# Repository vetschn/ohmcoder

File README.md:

# 

The `OHMCODER` is a 16 channel fully analog vocoder, housed in a 3U 19"
enclosure with a full patch bay and feed-through functionality.

This project is inspired by [this](https://www.instructables.com/Build-an-analog-vocoder/) instructables project by user [planetone](https://www.instructables.com/member/planetone/).

## Overview

In vocoders, a program and carrier signal are filtered into a number of
frequency bands. The envelope of the program signal bands then modulates
the carrier signal bands. Finally, the per-band contributions are summed
back together to get the vocoded output.

The core of the design thus made up of

- [Bandpass Filters](#multiple-feedback-infinite-gain-bandpass-filters)
- [Envelope Followers](#envelope-followers)
- [Voltage Controlled Amplifiers](#ota-voltage-controlled-amplifiers)

## Features

<!-- TODO -->

- Jack and XLR Input
- Patch Bay
- Per-Band Gain Control with LED Indicators
- Program or Carrier Band Feed-Through and/or Mixing
- Stereo and Mono Jack Output

## Circuits

### Multiple-Feedback Infinite Gain Bandpass Filters

We used the same second order multiple-feedback infinite-gain active
bandpass filters as in the instructibles project. TL074 quad opamps are
used.

Notice, that the nice thing about these filters is, that we only need to
change the capacitor values to get different center frequencies, as seen
in the SPICE simulation below.

#### Capacitor Values

| Band | f_low [Hz] | f_high [Hz] | C [nF] |
| ---- | ---------- | ----------- | ------ |
| 01   | 65         | 105         | 0.91   |
| 02   | 90         | 150         | 1.3    |
| 03   | 125        | 200         | 1.8    |
| 04   | 175        | 285         | 2.4    |
| 05   | 255        | 400         | 3.3    |
| 06   | 345        | 555         | 4.7    |
| 07   | 465        | 755         | 6.8    |
| 08   | 635        | 1050        | 9.1    |
| 09   | 920        | 1455        | 13     |
| 10   | 1220       | 1960        | 18     |
| 11   | 1765       | 2880        | 24     |
| 12   | 2500       | 4075        | 33     |
| 13   | 3515       | 5605        | 47     |
| 14   | 4640       | 7550        | 68     |
| 15   | 6375       | 10375       | 91     |
| 16   | 9200       | 15000       | 130    |

### Envelope Followers

This is where we depart from planetone's design. We use a low-pass
filtered precision rectifier signal to follow the program envelope.

The majority of the spectral energy of speech amplitude modulation lies
below about 15Hz, i. e. the mean time between syllables is about
1/15Hz (see [speech_modulation.ipynb](./auxiliary/notebooks/speech_modulation.ipynb) for an example). The filter is chosen such that we follow this
amplitude modulation.

### OTA Voltage Controlled Amplifiers

We use VCAs based on the LM13700 quad operational transconductance
amplifier, making use of its linearizing diodes and the integrated
buffer circuits.

The program envelope controls the amplifier gain via a voltage to
current converter circuit.

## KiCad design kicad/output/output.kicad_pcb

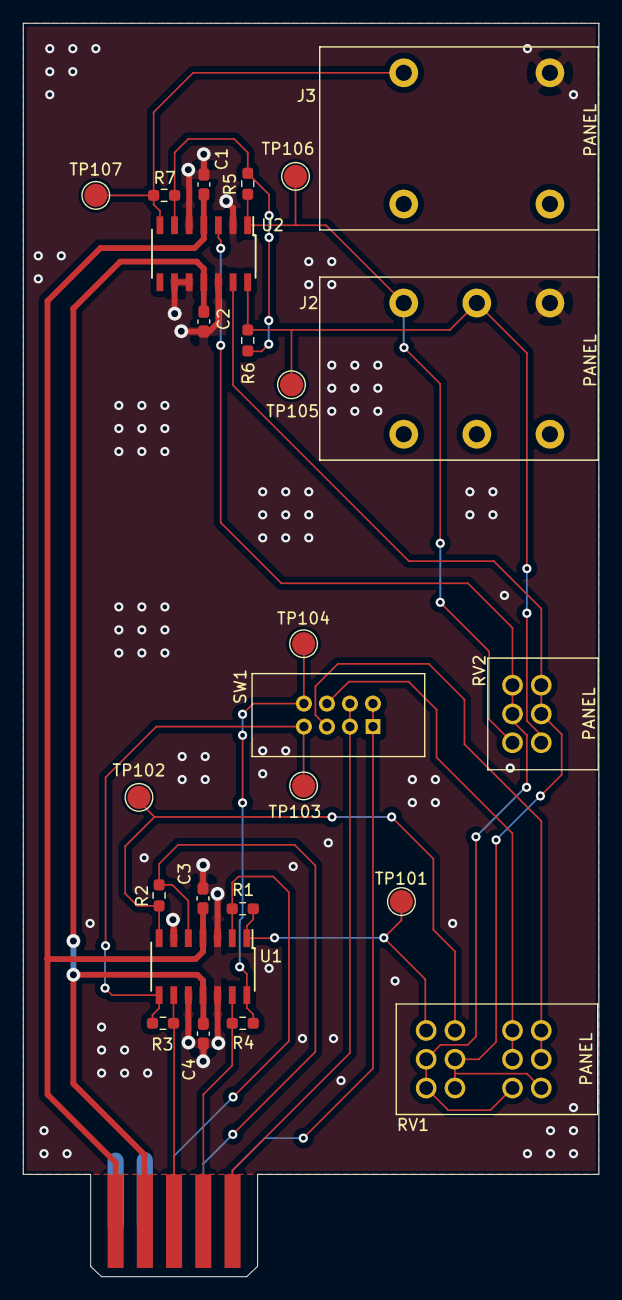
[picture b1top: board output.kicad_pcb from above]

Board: 2 copper layers, 50.0 x 108.9 mm, 26 parts (0 on the bottom side), 21 nets.

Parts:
C1, C2, C3, C4: 100n; C_0603_1608Metric_Pad1.08x0.95mm_HandSolder
J1: Conn_02x05_Odd_Even; 345-010-521-201_Male
J2: AudioJack3_Switch; Amphenol_ACJS-MHDRM
J3: AudioJack2_Switch; Amphenol_ACJM-MHDRM
R1, R2, R3, R4, R5, R6, R7: 10k; R_0603_1608Metric_Pad0.98x0.95mm_HandSolder
RV1: 10k; Bourns_PTD904-2020K-B103
RV2: 20k; Bourns_PTD902-2020K-A203
SW1: SW_DP3T; Hirose-DF51A-8DP-2DSA
TP101, TP102, TP103, TP104, TP105, TP106, TP107: TestPoint; TestPoint_Pad_D2.0mm
U1, U2: TL074; TL074-SOIC-14

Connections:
+12V: C1.1, C3.1, J1.1, U1.4, U2.4
-12V: C2.2, C4.2, J1.3, U1.11, U2.11
/CARRIER: J1.10, SW1.1, SW1.5
/FEEDTHROUGH_LEFT: RV1.R22, RV1.R23, SW1.7
/FEEDTHROUGH_RIGHT: RV1.R12, RV1.R13, SW1.3
/MOD_CARRIER_BANDS_LEFT: J1.6, R1.2, U1.2
/MOD_CARRIER_BANDS_LEFT_BUFFERED: R1.1, RV1.R43, TP101.1, U1.1
/MOD_CARRIER_BANDS_RIGHT: J1.8, R2.2, U1.5
/MOD_CARRIER_BANDS_RIGHT_BUFFERED: R2.1, RV1.R33, TP102.1, U1.7
/PROGRAM: J1.9, SW1.2, SW1.6
/PROGRAM_BANDS_LEFT: J1.5, R3.2, U1.9
/PROGRAM_BANDS_LEFT_BUFFERED: R3.1, SW1.4, TP103.1, U1.8
/PROGRAM_BANDS_RIGHT: J1.7, R4.2, U1.13
/PROGRAM_BANDS_RIGHT_BUFFERED: R4.1, SW1.8, TP104.1, U1.14
GND: C1.2, C2.1, C3.2, C4.1, J1.2, J1.4, J2.S, J3.S, U1.3, U1.6, U1.10, U1.12, U2.2, U2.5, U2.9, U2.10, U2.12
unnamed: J2.R, R6.2, RV2.4, TP105.1, U2.14
unnamed: J2.T, R5.1, RV2.1, TP106.1, U2.1
unnamed: J3.T, R7.2, TP107.1, U2.7
unnamed: R5.2, R6.1, R7.1, U2.6
unnamed: RV1.R11, RV1.R31, RV1.R32, RV2.5, RV2.6, U2.13
unnamed: RV1.R21, RV1.R41, RV1.R42, RV2.2, RV2.3, U2.3

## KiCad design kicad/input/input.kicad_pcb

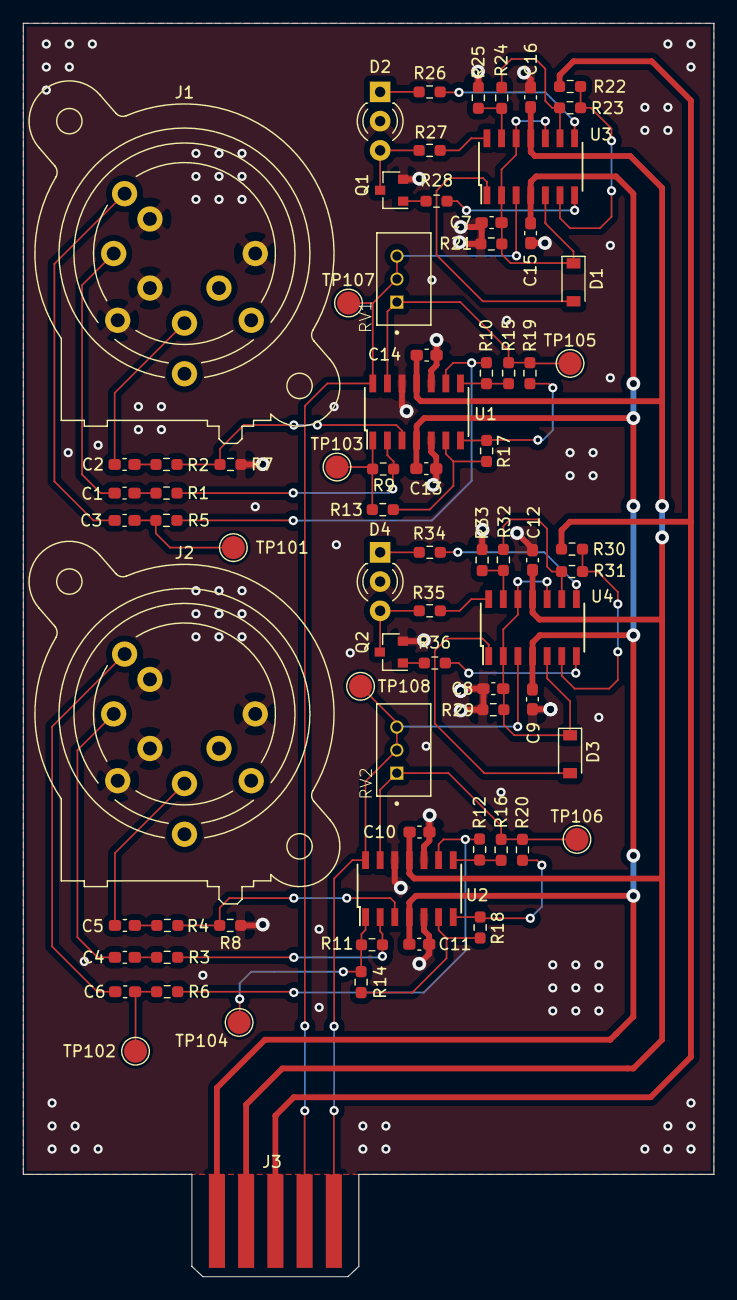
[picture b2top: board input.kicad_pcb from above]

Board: 2 copper layers, 60.0 x 108.9 mm, 75 parts (0 on the bottom side), 56 nets.

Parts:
C1, C2, C4, C5: 4.7u; C_0603_1608Metric_Pad1.08x0.95mm_HandSolder
C3, C6, C7, C8: 10u; C_0603_1608Metric_Pad1.08x0.95mm_HandSolder
C9, C10, C11, C12, C13, C14, C15, C16: 100n; C_0603_1608Metric_Pad1.08x0.95mm_HandSolder
D1, D3: 1N4148; D_SOD-123
D2, D4: LED_Dual_ACA; LED_D3.0mm-3
J1, J2: XLR3_AudioJack3_Combo_Switch; Jack_XLR-6.35mm_Neutrik_NCJ9FI-V_Vertical
J3: Conn_02x05_Odd_Even; 345-010-521-201_Male
Q1, Q2: MMBTA42; SOT-23
R1, R2, R3, R4, R13, R14, R28, R36: 1k; R_0603_1608Metric_Pad0.98x0.95mm_HandSolder
R5, R6, R7, R8, R9, R10, R11, R12, R15, R16, R17, R18, R19, R20: 10k; R_0603_1608Metric_Pad0.98x0.95mm_HandSolder
R21, R29: 4.7k; R_0603_1608Metric_Pad0.98x0.95mm_HandSolder
R22, R30: 27k; R_0603_1608Metric_Pad0.98x0.95mm_HandSolder
R23, R31: 18k; R_0603_1608Metric_Pad0.98x0.95mm_HandSolder
R24, R32: 33k; R_0603_1608Metric_Pad0.98x0.95mm_HandSolder
R25, R33: 22k; R_0603_1608Metric_Pad0.98x0.95mm_HandSolder
R26, R27, R34, R35: 470; R_0603_1608Metric_Pad0.98x0.95mm_HandSolder
RV1, RV2: 50k; TE-6-440054-3
TP101, TP102, TP103, TP104, TP105, TP106, TP107, TP108: TestPoint; TestPoint_Pad_D2.0mm
U1, U2, U3, U4: TL074; TL074-SOIC-14

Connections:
+2V: J3.5, R22.1, R30.1
+12V: C9.1, C11.1, C13.1, C15.1, J3.1, U1.4, U2.4, U3.4, U4.4
-12V: C10.2, C12.2, C14.2, C16.2, J3.3, U1.11, U2.11, U3.11, U4.11
/CARRIER: J3.9, RV2.2, RV2.3, TP108.1, U2.14, U4.3
/PROGRAM: J3.7, RV1.2, RV1.3, TP107.1, U1.14, U3.3
GND: C7.2, C8.2, C9.2, C10.1, C11.2, C12.1, C13.2, C14.1, C15.2, C16.1, D2.2, D4.2, J1.1, J1.S, J1.SN, J1.TN, J2.1, J2.S, J2.SN, J2.TN, J3.2, J3.4, J3.6, J3.8, J3.10, Q1.2, Q2.2, R7.2, R8.2, R21.2, R25.2, R29.2, R33.2, U1.5, U1.10, U1.12, U2.5, U2.10, U2.12
unnamed: C1.1, R1.2
unnamed: C1.2, J1.2
unnamed: C2.1, R2.2
unnamed: C2.2, J1.3
unnamed: C3.1, R5.2, TP101.1
unnamed: C3.2, J1.T
unnamed: C4.1, R3.2
unnamed: C4.2, J2.2
unnamed: C5.1, R4.2
unnamed: C5.2, J2.3
unnamed: C6.1, R6.2, TP102.1
unnamed: C6.2, J2.T
unnamed: C7.1, D1.1, R21.1, U3.2, U3.5, U3.10, U3.12
unnamed: C8.1, D3.1, R29.1, U4.2, U4.5, U4.10, U4.12
unnamed: D1.2, U3.1
unnamed: D2.1, R26.1
unnamed: D2.3, Q1.3, R27.1
unnamed: D3.2, U4.1
unnamed: D4.1, R34.1
unnamed: D4.3, Q2.3, R35.1
unnamed: Q1.1, R28.2
unnamed: Q2.1, R36.2
unnamed: R1.1, R9.2, U1.2
unnamed: R2.1, R7.1, U1.3
unnamed: R4.1, R8.1, U2.3
unnamed: R10.1, R15.1, U1.8
unnamed: R5.1, R10.2, U1.9
unnamed: R11.1, R14.2, TP104.1, U2.1
unnamed: R3.1, R11.2, U2.2
unnamed: R12.1, R16.1, U2.8
unnamed: R6.1, R12.2, U2.9
unnamed: R13.1, R17.2, U1.6
unnamed: R9.1, R13.2, TP103.1, U1.1
unnamed: R14.1, R18.2, U2.6
unnamed: R15.2, R19.1, RV1.1, TP105.1, U1.13
unnamed: R16.2, R20.1, RV2.1, TP106.1, U2.13
unnamed: R17.1, R19.2, U1.7
unnamed: R18.1, R20.2, U2.7
unnamed: R22.2, R23.1, U3.6
unnamed: R23.2, R24.1, U3.9
unnamed: R24.2, R25.1, U3.13
unnamed: R26.2, U3.8
unnamed: R27.2, U3.14
unnamed: R28.1, U3.7
unnamed: R30.2, R31.1, U4.6
unnamed: R31.2, R32.1, U4.9
unnamed: R32.2, R33.1, U4.13
unnamed: R34.2, U4.8
unnamed: R35.2, U4.14
unnamed: R36.1, U4.7

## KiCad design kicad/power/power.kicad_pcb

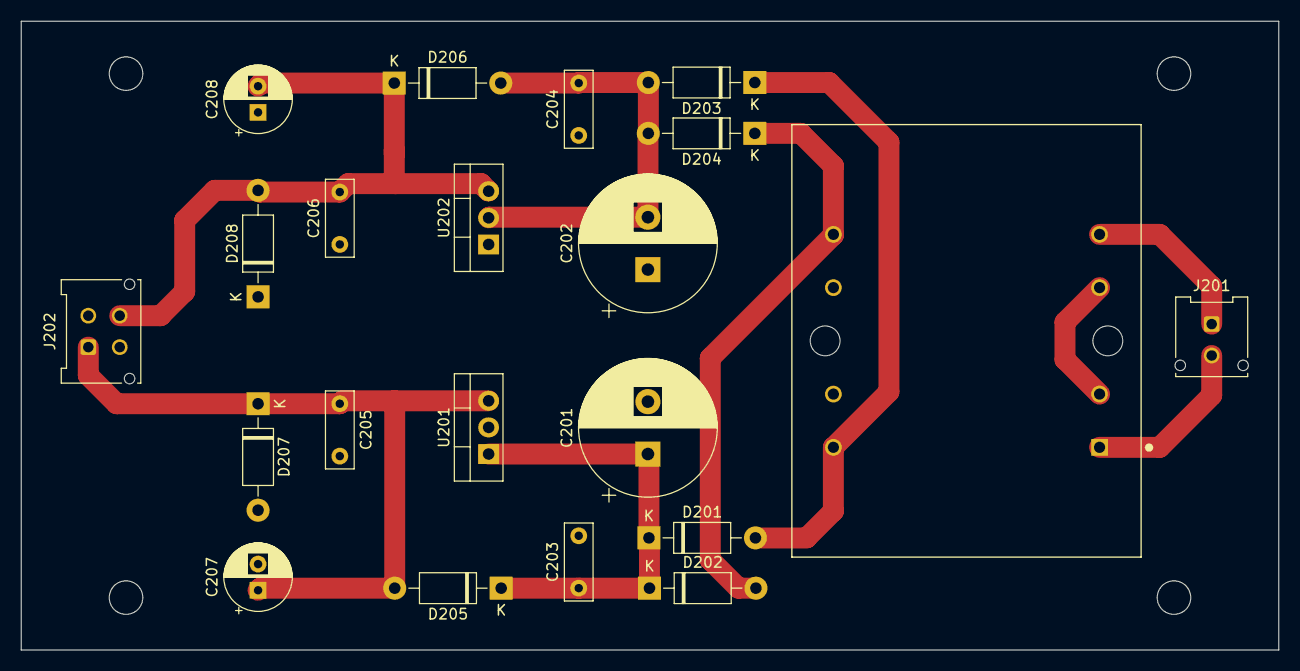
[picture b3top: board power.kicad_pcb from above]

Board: 2 copper layers, 120.0 x 60.0 mm, 21 parts (0 on the bottom side), 10 nets.

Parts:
C201, C202: 2200u; CP_Radial_D13.0mm_P5.00mm
C203, C204, C205, C206: 100n; C_Rect_L7.2mm_W2.5mm_P5.00mm_FKS2_FKP2_MKS2_MKP2
C207, C208: 100u; CP_Radial_D6.3mm_P2.50mm
D201, D202, D203, D204, D205, D206, D207, D208: 1N4002; D_DO-41_SOD81_P10.16mm_Horizontal
J201: Conn_01x02_Female; Molex_Micro-Fit_3.0_43045-0212_2x01_P3.00mm_Vertical
J202: Conn_02x02_Odd_Even; Molex_Micro-Fit_3.0_43045-0412_2x02_P3.00mm_Vertical
T201: VPP36-140; XFMR_VPP36-140
U201: uA7812; TO-220-3_Vertical
U202: uA7912; TO-220-3_Vertical

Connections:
+12V: C205.1, C207.1, D205.2, D207.1, J202.1, U201.3
-12V: C206.2, C208.2, D206.1, D208.2, J202.4, U202.3
GND: C201.2, C202.1, C203.2, C204.1, C205.2, C206.1, C207.2, C208.1, D207.2, D208.1, J202.2, J202.3, T201.9, T201.10, U201.2, U202.1
unnamed: C201.1, C203.1, D201.1, D202.1, D205.1, U201.1
unnamed: C202.2, C204.2, D203.2, D204.2, D206.2, U202.2
unnamed: D201.2, D203.1, T201.7
unnamed: D202.2, D204.1, T201.12
unnamed: J201.1, T201.6
unnamed: J201.2, T201.1
unnamed: T201.3, T201.4

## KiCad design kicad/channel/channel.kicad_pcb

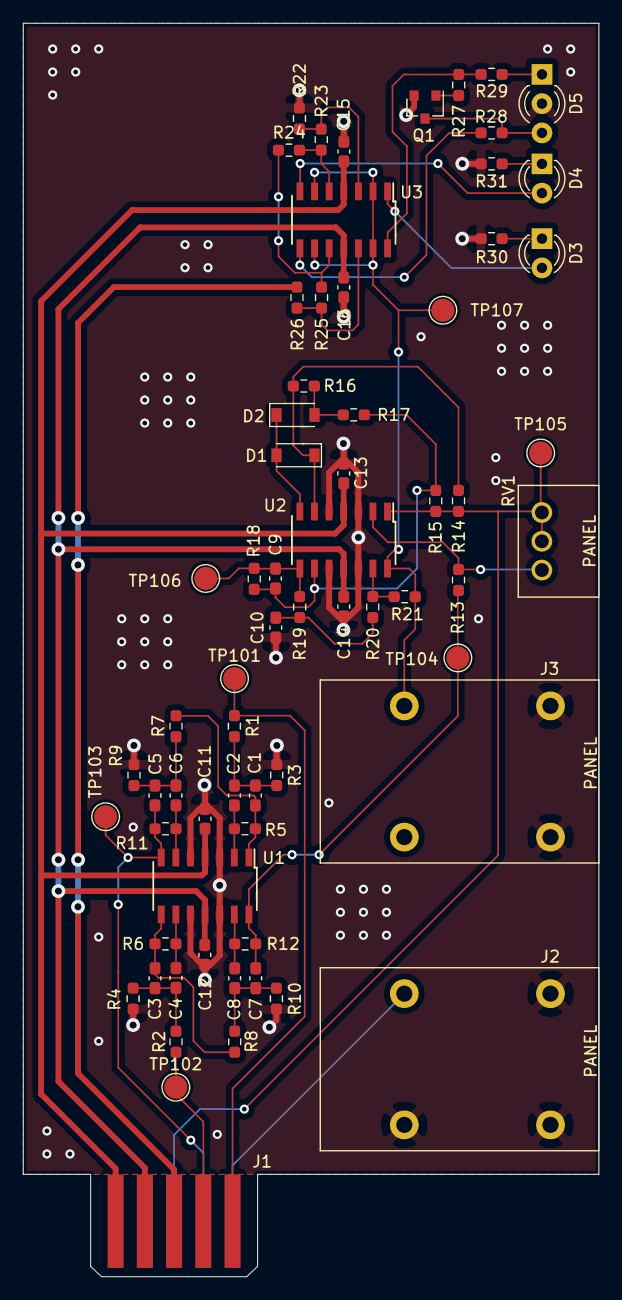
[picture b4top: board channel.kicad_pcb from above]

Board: 2 copper layers, 50.0 x 108.9 mm, 67 parts (0 on the bottom side), 42 nets.

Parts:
C1, C2, C3, C4, C5, C6, C7, C8: X; C_0603_1608Metric_Pad1.08x0.95mm_HandSolder
C9, C10: 680n; C_0603_1608Metric_Pad1.08x0.95mm_HandSolder
C11, C12, C13, C14, C15, C16: 100n; C_0603_1608Metric_Pad1.08x0.95mm_HandSolder
D1, D2: 1N4148; D_SOD-123
D3, D4: LED; LED_D3.0mm
D5: LED_Dual_ACA; LED_D3.0mm-3
J1: Conn_02x05_Odd_Even; 345-010-521-201_Male
J2, J3: AudioJack2_Switch; Amphenol_ACJM-MHDRM
Q1: MMBTA42; SOT-23
R1, R2: 33k; R_0603_1608Metric_Pad0.98x0.95mm_HandSolder
R3, R4: 2k; R_0603_1608Metric_Pad0.98x0.95mm_HandSolder
R5, R6: 200k; R_0603_1608Metric_Pad0.98x0.95mm_HandSolder
R7, R8: 20k; R_0603_1608Metric_Pad0.98x0.95mm_HandSolder
R9, R10: 1.2k; R_0603_1608Metric_Pad0.98x0.95mm_HandSolder
R11, R12: 120k; R_0603_1608Metric_Pad0.98x0.95mm_HandSolder
R13: 50k; R_0603_1608Metric_Pad0.98x0.95mm_HandSolder
R14, R15, R16, R17, R18, R19: 10k; R_0603_1608Metric_Pad0.98x0.95mm_HandSolder
R20, R21: 100k; R_0603_1608Metric_Pad0.98x0.95mm_HandSolder
R22: 4.7k; R_0603_1608Metric_Pad0.98x0.95mm_HandSolder
R23: 18k; R_0603_1608Metric_Pad0.98x0.95mm_HandSolder
R24, R25, R26: 27k; R_0603_1608Metric_Pad0.98x0.95mm_HandSolder
R27: 1k; R_0603_1608Metric_Pad0.98x0.95mm_HandSolder
R28, R29, R30, R31: 470; R_0603_1608Metric_Pad0.98x0.95mm_HandSolder
RV1: 100k; Bourns_PTD901-2015K-A104
TP101, TP102, TP103, TP104, TP105, TP106, TP107: TestPoint; TestPoint_Pad_D2.0mm
U1, U2, U3: TL074; TL074-SOIC-14

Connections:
+12V: C11.1, C13.1, C15.1, J1.1, U1.4, U2.4, U3.4
-2V: J1.5, R26.2
-12V: C12.2, C14.2, C16.2, J1.3, U1.11, U2.11, U3.11
/BAND_LEDS/IN: J3.T, R21.1, TP107.1, U2.14, U3.2, U3.6, U3.9, U3.13
/CARRIER: J1.9, R1.2, TP101.1
/CARRIER_BAND: C5.1, J1.8, R11.2, TP103.1, U1.7
/PROGRAM: J1.7, R2.2, TP102.1
/PROGRAM_BAND: J1.6, R14.2, R15.2, RV1.2, RV1.3, TP105.1, U2.1
/PROGRAM_ENV: J1.10, J2.T
GND: C10.1, C11.2, C12.1, C13.2, C14.1, C15.2, C16.1, D5.2, J1.2, J1.4, J2.S, J2.SN, J2.TN, J3.S, J3.SN, Q1.2, R3.1, R4.1, R9.1, R10.1, R22.1, R30.1, R31.1, U1.3, U1.5, U1.10, U1.12, U2.3, U2.5, U2.10, U2.12
unnamed: C1.1, R5.2, R7.2, U1.1
unnamed: C1.2, C2.2, R1.1, R3.2
unnamed: C2.1, R5.1, U1.2
unnamed: C3.1, R6.2, R8.2, U1.8
unnamed: C3.2, C4.2, R2.1, R4.2
unnamed: C4.1, R6.1, U1.9
unnamed: C5.2, C6.2, R7.1, R9.2
unnamed: C6.1, R11.1, U1.6
unnamed: C7.1, R12.2, R13.2, TP104.1, U1.14
unnamed: C7.2, C8.2, R8.1, R10.2
unnamed: C8.1, R12.1, U1.13
unnamed: C9.1, R18.1, R19.2, TP106.1, U2.8
unnamed: C9.2, R15.1, R17.1, R18.2, U2.9
unnamed: C10.2, R19.1, R20.2
unnamed: D1.1, R14.1, R16.2, U2.6
unnamed: D1.2, D2.1, U2.7
unnamed: D2.2, R16.1, R17.2
unnamed: D3.1, R30.2
unnamed: D3.2, U3.1
unnamed: D4.1, R31.2
unnamed: D4.2, U3.7
unnamed: D5.1, R29.1
unnamed: D5.3, Q1.3, R28.1
unnamed: Q1.1, R27.1
unnamed: R13.1, RV1.1, U2.2
unnamed: R20.1, R21.2, U2.13
unnamed: R22.2, R23.1, U3.3
unnamed: R23.2, R24.1, U3.5
unnamed: R24.2, R25.1, U3.10
unnamed: R25.2, R26.1, U3.12
unnamed: R27.2, R29.2, U3.14
unnamed: R28.2, U3.8

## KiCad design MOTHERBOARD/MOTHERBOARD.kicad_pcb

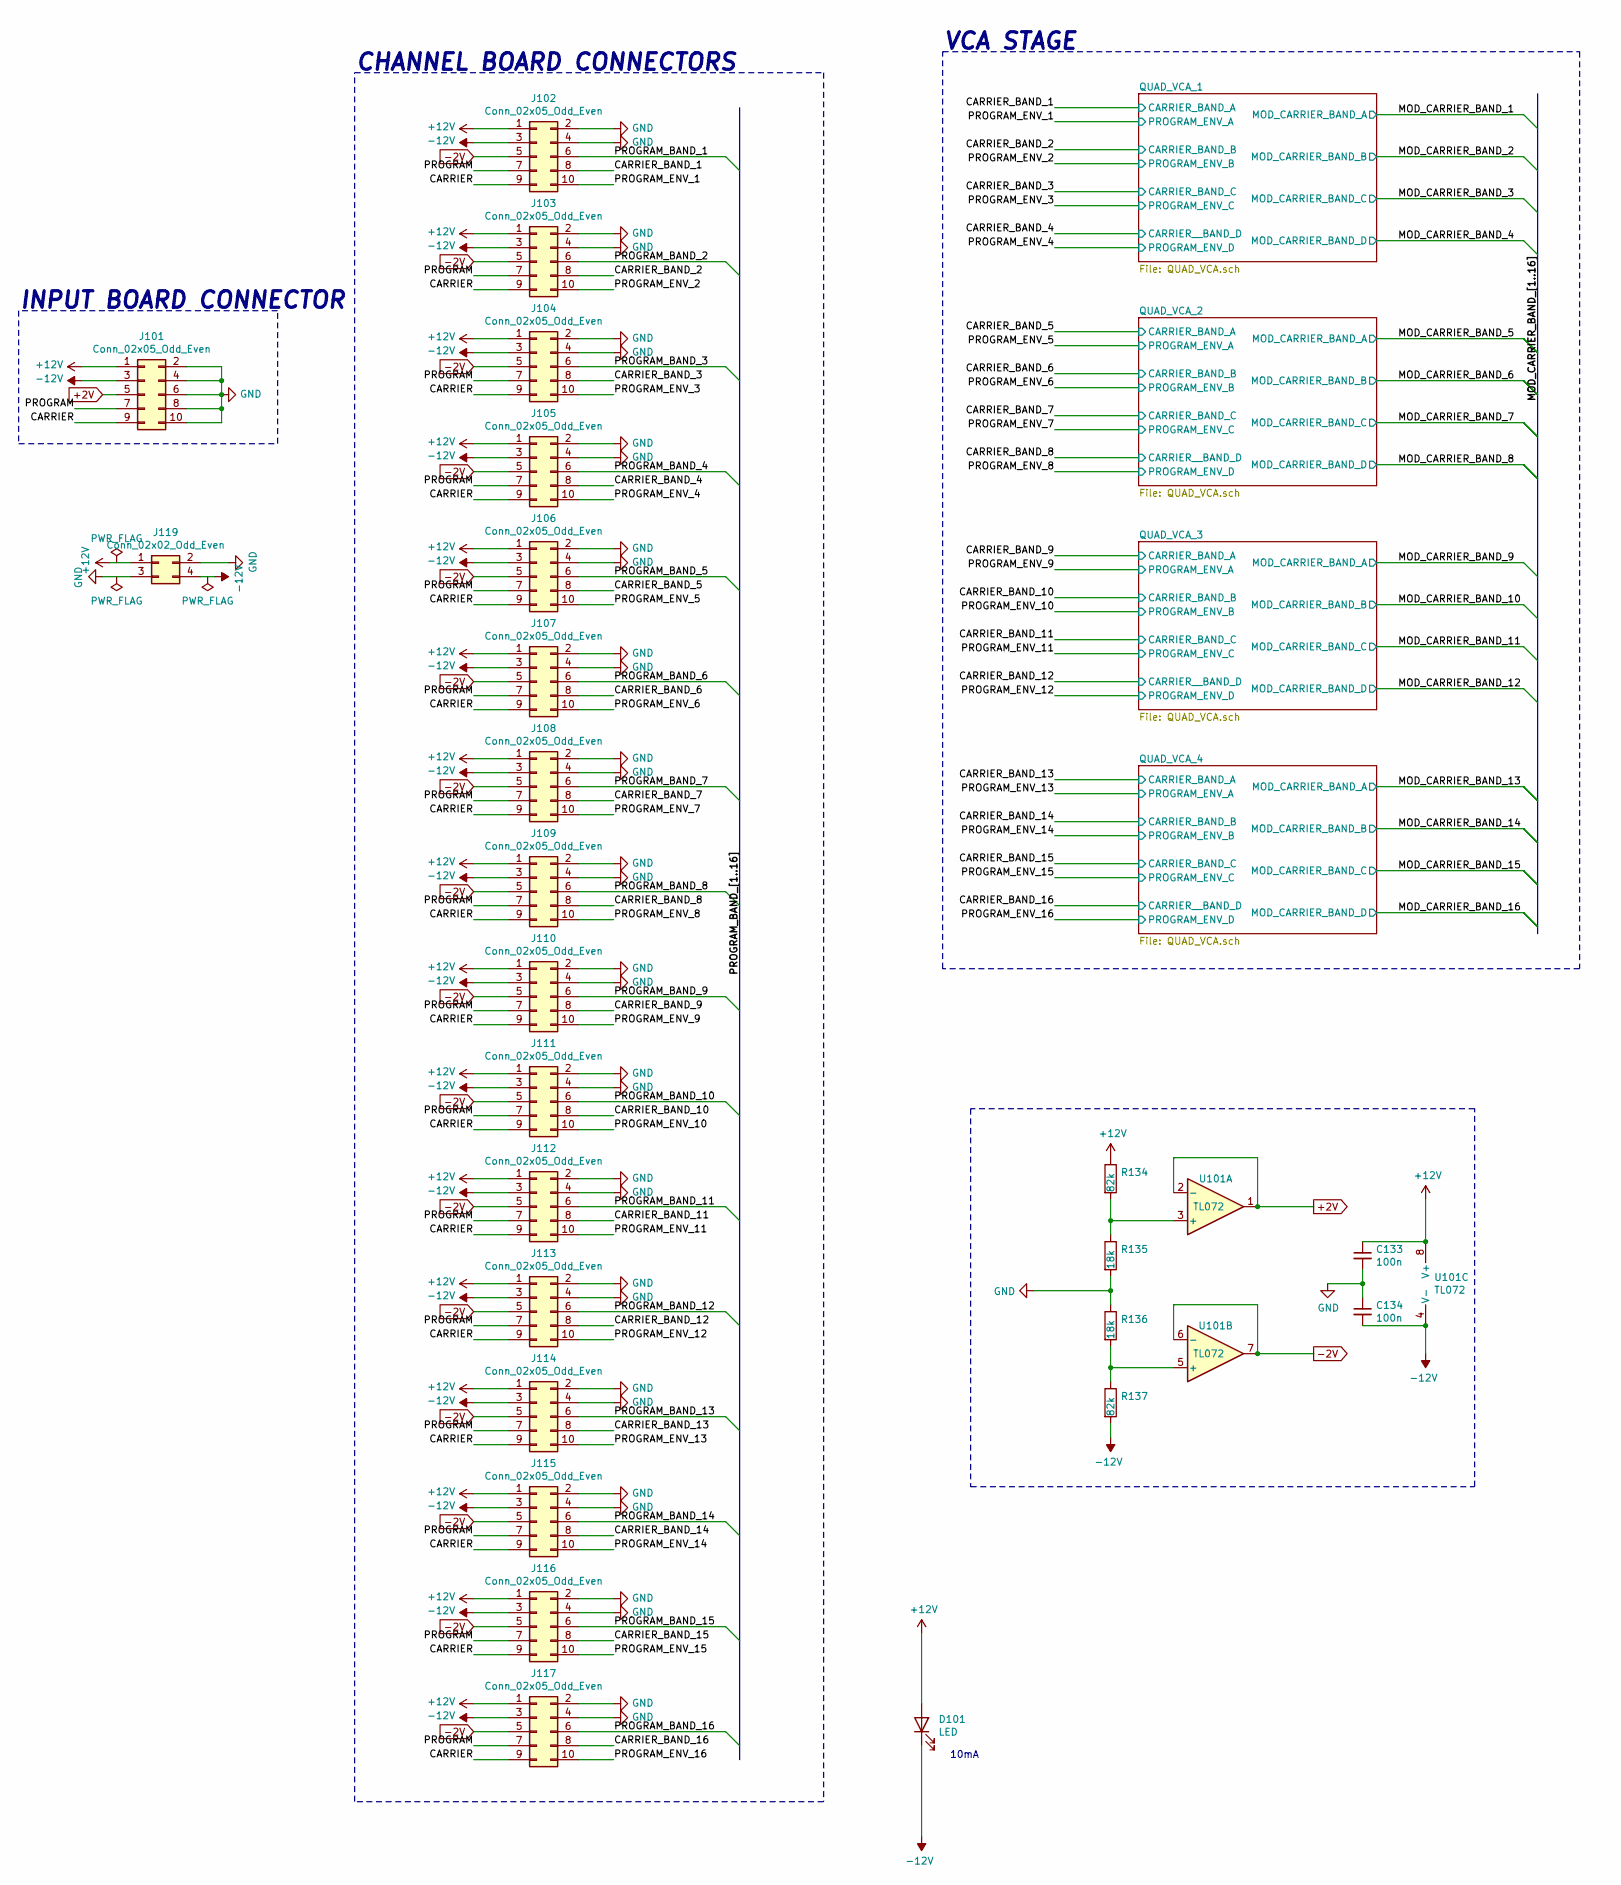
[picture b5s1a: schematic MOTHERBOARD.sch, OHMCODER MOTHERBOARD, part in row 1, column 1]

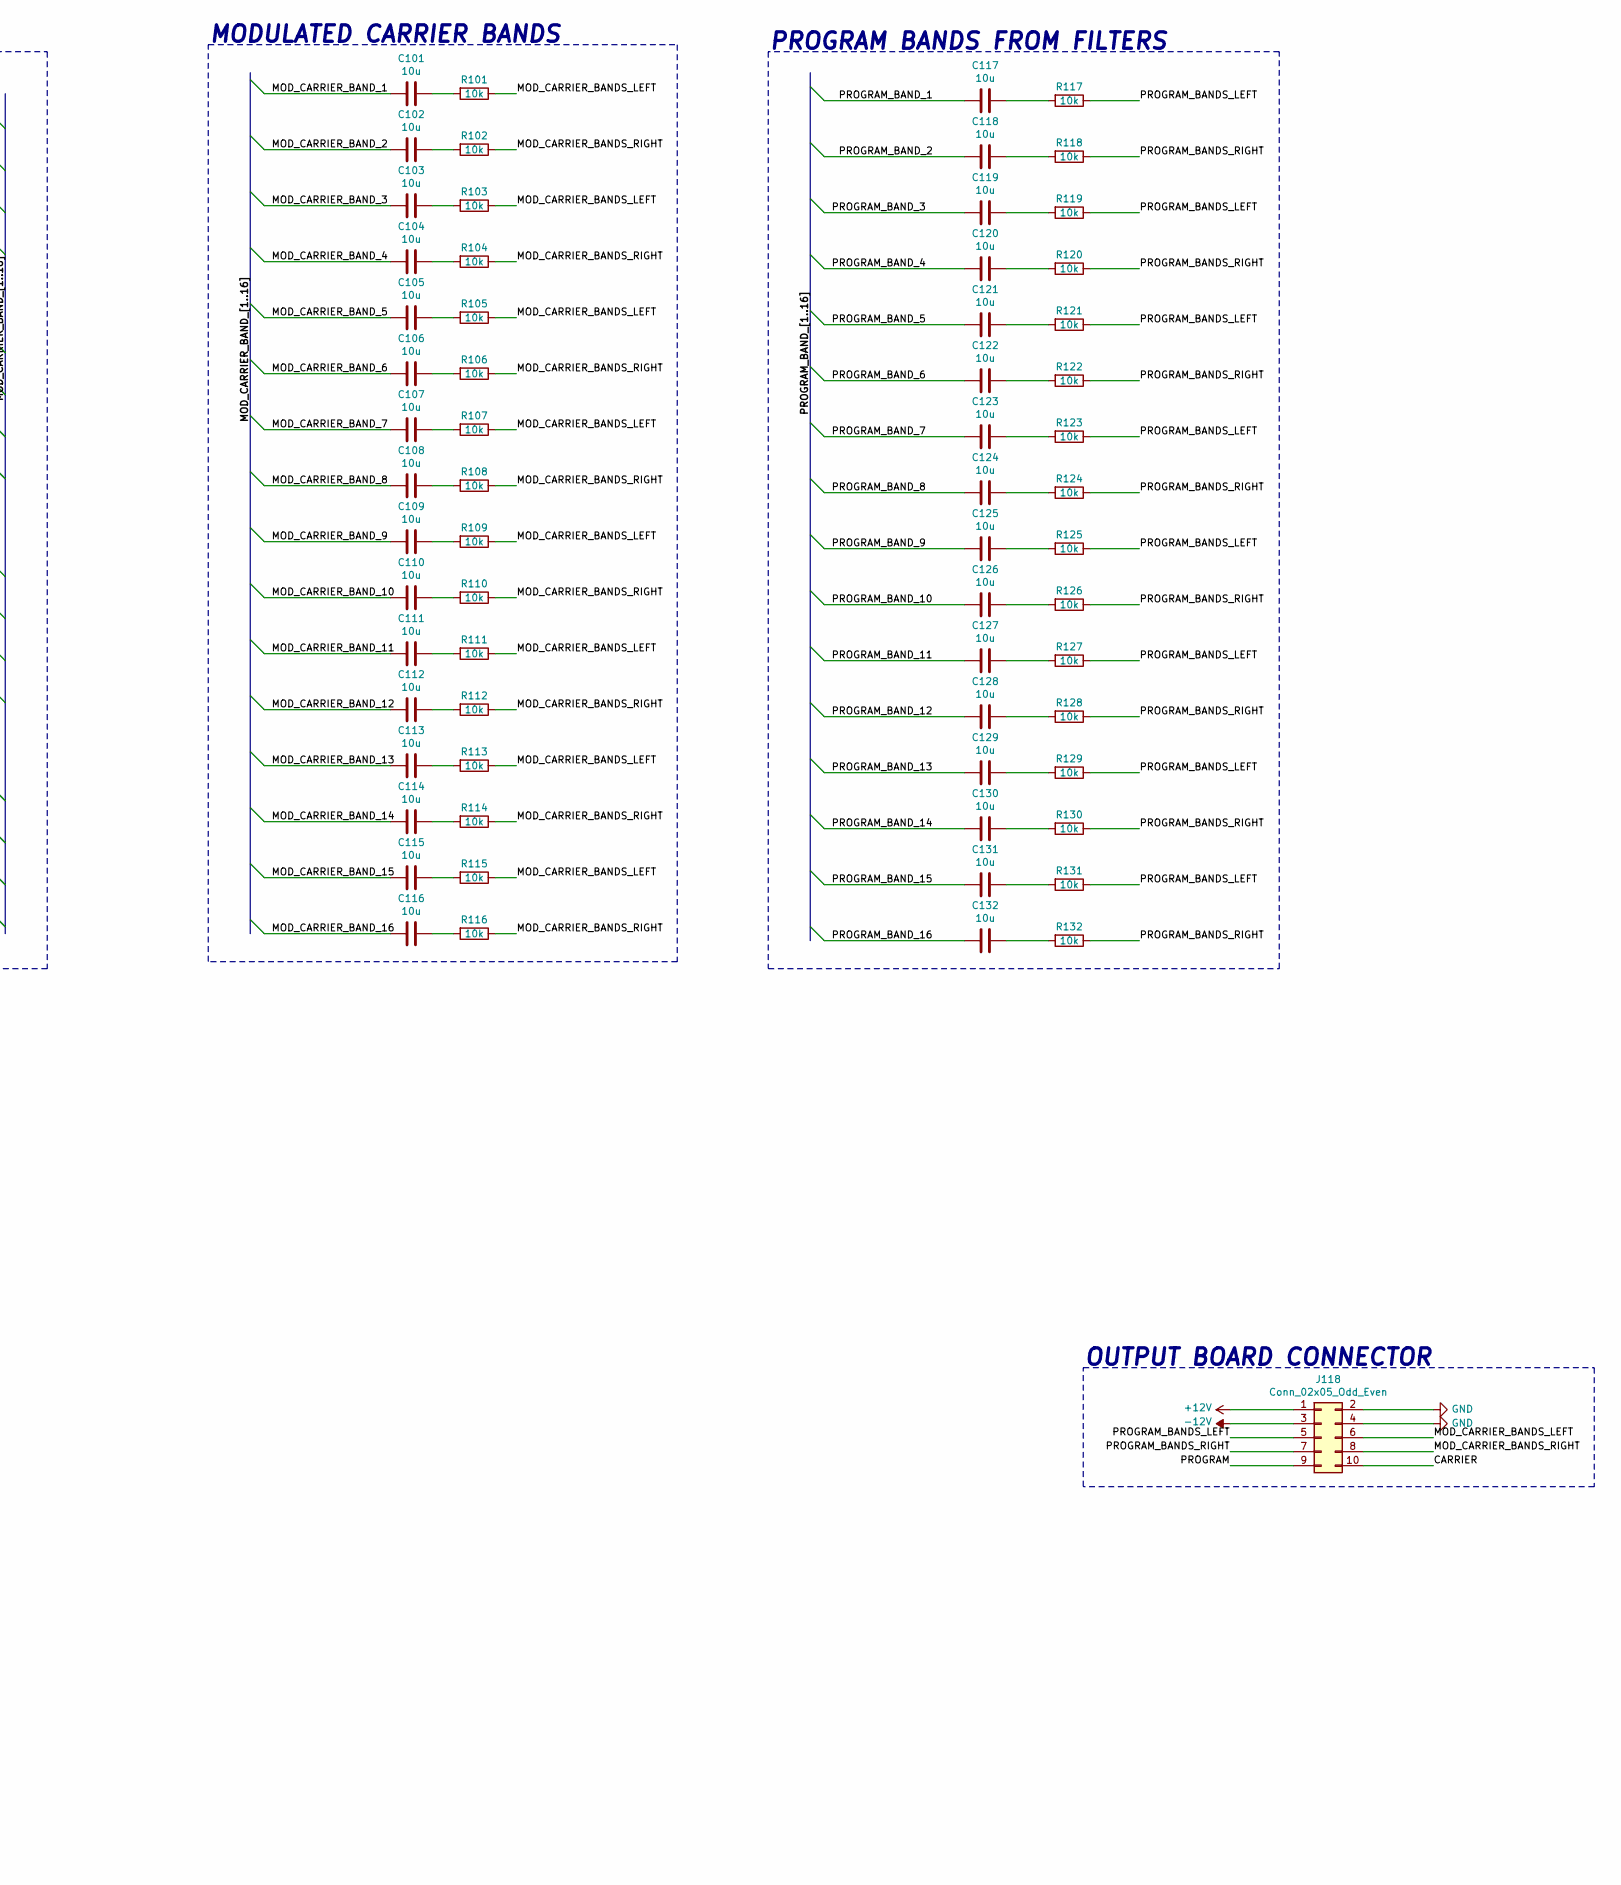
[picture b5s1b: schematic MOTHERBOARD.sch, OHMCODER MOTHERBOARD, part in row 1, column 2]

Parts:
C101, C102, C103, C104, C105, C106, C107, C108, C109, C110, C111, C112, C113, C114, C115, C116, C117, C118, C119, C120, C121, C122, C123, C124, C125, C126, C127, C128, C129, C130, C131, C132: 10u; C_0603_1608Metric_Pad1.08x0.95mm_HandSolder
C133, C134: 100n; C_0603_1608Metric_Pad1.08x0.95mm_HandSolder
D101: LED; TE-6-440054-3
J101, J102, J103, J104, J105, J106, J107, J108, J109, J110, J111, J112, J113, J114, J115, J116, J117, J118: Conn_02x05_Odd_Even; 345-010-521-201_Female
J119: Conn_02x02_Odd_Even; Molex_Micro-Fit_3.0_43045-0412_2x02_P3.00mm_Vertical
R101, R102, R103, R104, R105, R106, R107, R108, R109, R110, R111, R112, R113, R114, R115, R116, R117, R118, R119, R120, R121, R122, R123, R124, R125, R126, R127, R128, R129, R130, R131, R132: 10k; R_0603_1608Metric_Pad0.98x0.95mm_HandSolder
R134, R137: 82k; R_0603_1608Metric_Pad0.98x0.95mm_HandSolder
R135, R136: 18k; R_0603_1608Metric_Pad0.98x0.95mm_HandSolder
U101: TL072; TL072-SOIC-8

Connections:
+2V: J101.5, U101.1, U101.2 (-)
+12V: C133.1, D101.2 (A), J101.1, J102.1, J103.1, J104.1, J105.1, J106.1, J107.1, J108.1, J109.1, J110.1, J111.1, J112.1, J113.1, J114.1, J115.1, J116.1, J117.1, J118.1, J119.1, R134.1, U101.8 (V+); also elsewhere on the board
-2V: J102.5, J103.5, J104.5, J105.5, J106.5, J107.5, J108.5, J109.5, J110.5, J111.5, J112.5, J113.5, J114.5, J115.5, J116.5, J117.5, U101.6 (-), U101.7
/CARRIER: J101.9, J102.9, J103.9, J104.9, J105.9, J106.9, J107.9, J108.9, J109.9, J110.9, J111.9, J112.9, J113.9, J114.9, J115.9, J116.9, J117.9, J118.10
/CARRIER_BAND_1: J102.8; also elsewhere on the board
/CARRIER_BAND_2: J103.8; also elsewhere on the board
/CARRIER_BAND_3: J104.8; also elsewhere on the board
/CARRIER_BAND_4: J105.8; also elsewhere on the board
/CARRIER_BAND_5: J106.8; also elsewhere on the board
/CARRIER_BAND_6: J107.8; also elsewhere on the board
/CARRIER_BAND_7: J108.8; also elsewhere on the board
/CARRIER_BAND_8: J109.8; also elsewhere on the board
/CARRIER_BAND_9: J110.8; also elsewhere on the board
/CARRIER_BAND_10: J111.8; also elsewhere on the board
/CARRIER_BAND_11: J112.8; also elsewhere on the board
/CARRIER_BAND_12: J113.8; also elsewhere on the board
/CARRIER_BAND_13: J114.8; also elsewhere on the board
/CARRIER_BAND_14: J115.8; also elsewhere on the board
/CARRIER_BAND_15: J116.8; also elsewhere on the board
/CARRIER_BAND_16: J117.8; also elsewhere on the board
/MOD_CARRIER_BANDS_LEFT: J118.6, R101.1, R103.1, R105.1, R107.1, R109.1, R111.1, R113.1, R115.1
/MOD_CARRIER_BANDS_RIGHT: J118.8, R102.1, R104.1, R106.1, R108.1, R110.1, R112.1, R114.1, R116.1
/MOD_CARRIER_BAND_1: C101.2; also elsewhere on the board
/MOD_CARRIER_BAND_2: C102.2; also elsewhere on the board
/MOD_CARRIER_BAND_3: C103.2; also elsewhere on the board
/MOD_CARRIER_BAND_4: C104.2; also elsewhere on the board
/MOD_CARRIER_BAND_5: C105.2; also elsewhere on the board
/MOD_CARRIER_BAND_6: C106.2; also elsewhere on the board
/MOD_CARRIER_BAND_7: C107.2; also elsewhere on the board
/MOD_CARRIER_BAND_8: C108.2; also elsewhere on the board
/MOD_CARRIER_BAND_9: C109.2; also elsewhere on the board
/MOD_CARRIER_BAND_10: C110.2; also elsewhere on the board
/MOD_CARRIER_BAND_11: C111.2; also elsewhere on the board
/MOD_CARRIER_BAND_12: C112.2; also elsewhere on the board
/MOD_CARRIER_BAND_13: C113.2; also elsewhere on the board
/MOD_CARRIER_BAND_14: C114.2; also elsewhere on the board
/MOD_CARRIER_BAND_15: C115.2; also elsewhere on the board
/MOD_CARRIER_BAND_16: C116.2; also elsewhere on the board
/PROGRAM: J101.7, J102.7, J103.7, J104.7, J105.7, J106.7, J107.7, J108.7, J109.7, J110.7, J111.7, J112.7, J113.7, J114.7, J115.7, J116.7, J117.7, J118.9
/PROGRAM_BANDS_LEFT: J118.5, R117.1, R119.1, R121.1, R123.1, R125.1, R127.1, R129.1, R131.1
/PROGRAM_BANDS_RIGHT: J118.7, R118.1, R120.1, R122.1, R124.1, R126.1, R128.1, R130.1, R132.1
/PROGRAM_BAND_1: C117.2, J102.6
/PROGRAM_BAND_2: C118.2, J103.6
/PROGRAM_BAND_3: C119.2, J104.6
/PROGRAM_BAND_4: C120.2, J105.6
/PROGRAM_BAND_5: C121.2, J106.6
/PROGRAM_BAND_6: C122.2, J107.6
/PROGRAM_BAND_7: C123.2, J108.6
/PROGRAM_BAND_8: C124.2, J109.6
/PROGRAM_BAND_9: C125.2, J110.6
/PROGRAM_BAND_10: C126.2, J111.6
/PROGRAM_BAND_11: C127.2, J112.6
/PROGRAM_BAND_12: C128.2, J113.6
/PROGRAM_BAND_13: C129.2, J114.6
/PROGRAM_BAND_14: C130.2, J115.6
/PROGRAM_BAND_15: C131.2, J116.6
/PROGRAM_BAND_16: C132.2, J117.6
/PROGRAM_ENV_1: J102.10; also elsewhere on the board
/PROGRAM_ENV_2: J103.10; also elsewhere on the board
/PROGRAM_ENV_3: J104.10; also elsewhere on the board
/PROGRAM_ENV_4: J105.10; also elsewhere on the board
/PROGRAM_ENV_5: J106.10; also elsewhere on the board
/PROGRAM_ENV_6: J107.10; also elsewhere on the board
/PROGRAM_ENV_7: J108.10; also elsewhere on the board
/PROGRAM_ENV_8: J109.10; also elsewhere on the board
/PROGRAM_ENV_9: J110.10; also elsewhere on the board
/PROGRAM_ENV_10: J111.10; also elsewhere on the board
/PROGRAM_ENV_11: J112.10; also elsewhere on the board
/PROGRAM_ENV_12: J113.10; also elsewhere on the board
/PROGRAM_ENV_13: J114.10; also elsewhere on the board
/PROGRAM_ENV_14: J115.10; also elsewhere on the board
/PROGRAM_ENV_15: J116.10; also elsewhere on the board
/PROGRAM_ENV_16: J117.10; also elsewhere on the board
GND: C133.2, C134.1, J101.2, J101.4, J101.6, J101.8, J101.10, J102.2, J102.4, J103.2, J103.4, J104.2, J104.4, J105.2, J105.4, J106.2, J106.4, J107.2, J107.4, J108.2, J108.4, J109.2, J109.4, J110.2, J110.4, J111.2, J111.4, J112.2, J112.4, J113.2, J113.4, J114.2, J114.4, J115.2, J115.4, J116.2, J116.4, J117.2, J117.4, J118.2, J118.4, J119.2, J119.3, R135.2, R136.1; also elsewhere on the board
unnamed: C101.1, R101.2
unnamed: C102.1, R102.2
unnamed: C103.1, R103.2
unnamed: C104.1, R104.2
unnamed: C105.1, R105.2
unnamed: C106.1, R106.2
unnamed: C107.1, R107.2
unnamed: C108.1, R108.2
unnamed: C109.1, R109.2
unnamed: C110.1, R110.2
unnamed: C111.1, R111.2
unnamed: C112.1, R112.2
unnamed: C113.1, R113.2
unnamed: C114.1, R114.2
unnamed: C115.1, R115.2
unnamed: C116.1, R116.2
unnamed: C117.1, R117.2
unnamed: C118.1, R118.2
unnamed: C119.1, R119.2
unnamed: C120.1, R120.2
unnamed: C121.1, R121.2
unnamed: C122.1, R122.2
unnamed: C123.1, R123.2
unnamed: C124.1, R124.2
unnamed: C125.1, R125.2
unnamed: C126.1, R126.2
unnamed: C127.1, R127.2
unnamed: C128.1, R128.2
unnamed: C129.1, R129.2
unnamed: C130.1, R130.2
unnamed: C131.1, R131.2
unnamed: C132.1, R132.2
unnamed: R134.2, R135.1, U101.3 (+)
unnamed: R136.2, R137.1, U101.5 (+)

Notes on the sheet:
MODULATED CARRIER BANDS
PROGRAM BANDS FROM FILTERS
VCA STAGE
CHANNEL BOARD CONNECTORS
OUTPUT BOARD CONNECTOR
INPUT BOARD CONNECTOR
10mA
